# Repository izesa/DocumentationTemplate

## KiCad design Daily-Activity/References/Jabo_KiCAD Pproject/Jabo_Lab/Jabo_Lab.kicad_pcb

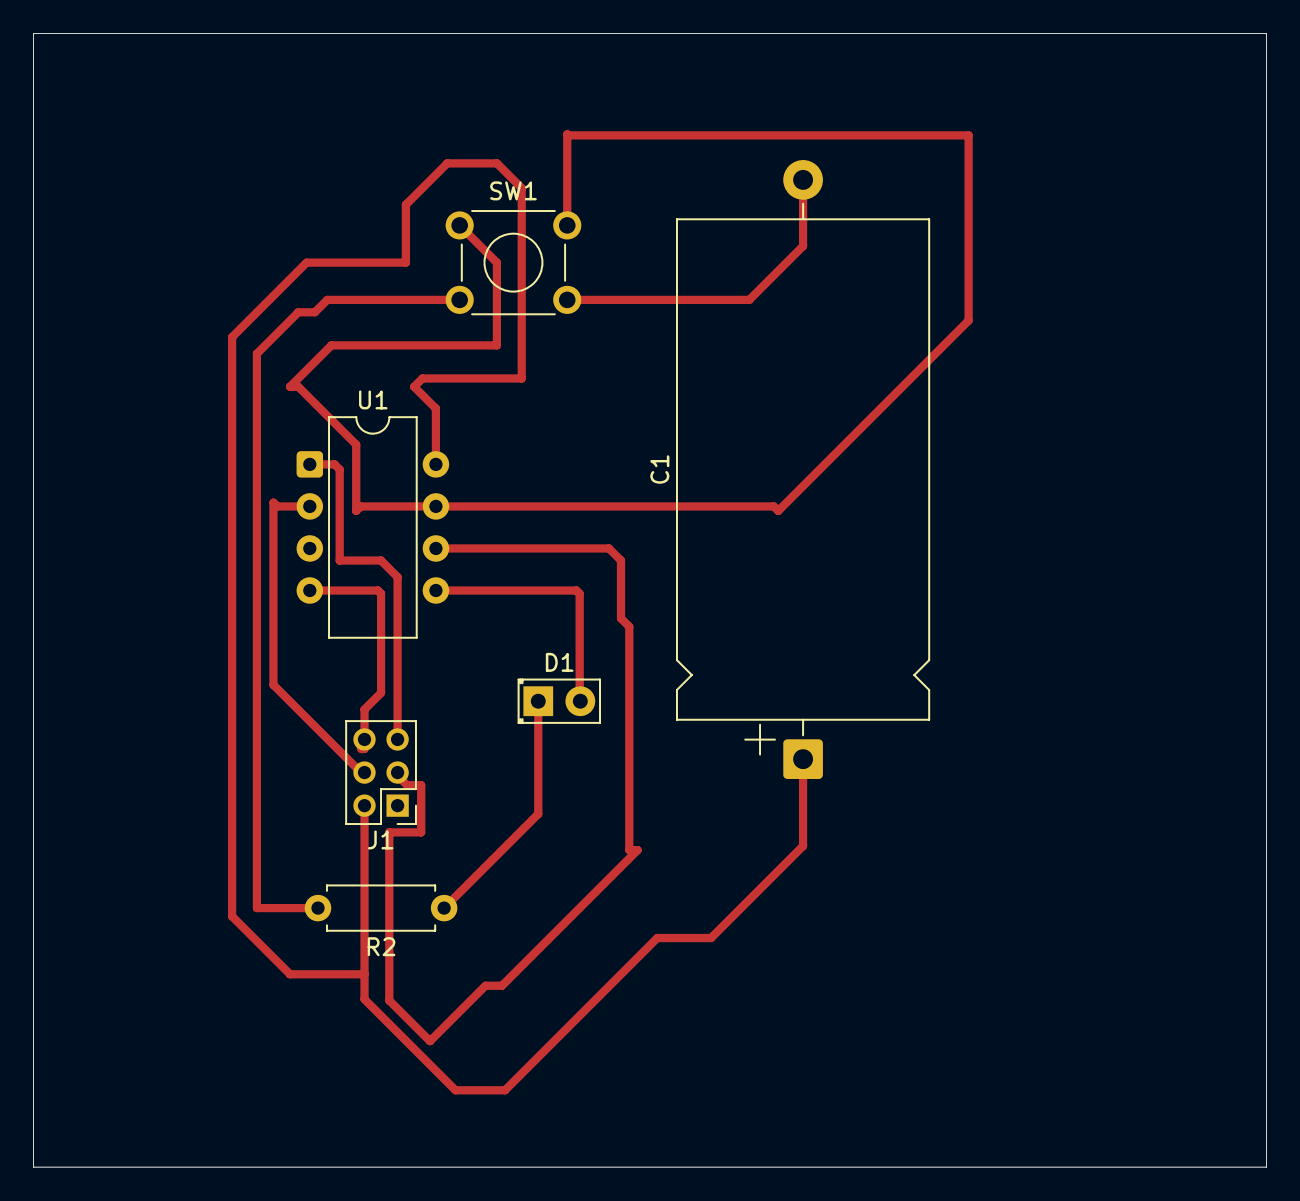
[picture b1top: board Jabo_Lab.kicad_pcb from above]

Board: 2 copper layers, 74.5 x 68.5 mm, 6 parts (0 on the bottom side), 9 nets.

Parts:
C1: 0.1 µF; CP_Axial_L30.0mm_D15.0mm_P35.00mm_Horizontal
D1: LED; LED_D2.0mm_W4.8mm_H2.5mm_FlatTop
J1: AVR-ISP-6; PinHeader_2x03_P2.00mm_Vertical
R2: 220Ohm; R_Axial_DIN0207_L6.3mm_D2.5mm_P7.62mm_Horizontal
SW1: SW_Push; SW_TH_Tactile_Omron_B3F-102x
U1: ATtiny45-20P; CERDIP-8_W7.62mm_SideBrazed

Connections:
5V: C1.1, J1.2 (VCC), U1.8 (VCC)
GND: C1.2, J1.6 (GND), R2.2, SW1.2, U1.4 (GND)
unnamed: D1.2 (A), U1.5 (AREF/PB0)
unnamed: D1.1 (K), R2.1
unnamed: J1.0 (MISO), U1.3 (XTAL2/PB4)
unnamed: J1.4 (MOSI), U1.2 (XTAL1/PB3)
unnamed: J1.3 (SCK), U1.6 (PB1)
unnamed: J1.5 (~RST), U1.1 (~RESET/PB5)
unnamed: SW1.1, U1.7 (PB2)

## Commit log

2026-01-27 the image of IZESA_Jabo in the docs folder will be used at the home page.
2026-01-27 modified: docs/index.md
2026-01-27 renamed: docs/IZESA_Jabo.JPG -> docs/images/IZESA_Jabo.JPG
2026-01-27 modified: docs/index.md
2026-01-27 modified: docs/index.md modified: mkdocs.yml
2026-01-27 modified: docs/Daily-Activity/day_1.md
2026-01-27 new file: docs/Daily-Activity/FreeCad.jpg modified: docs/Daily-Activity/day_2.md
2026-01-27 modified: docs/Daily-Activity/day_2.md renamed: docs/Daily-Activity/FreeCad.jpg -> m docs/files/FreeCad.jpg
2026-01-27 modified: docs/Daily-Activity/day_2.md renamed: docs/files/FreeCad.jpg -> docs/images/FreeCad.jpg
2026-01-27 modified: docs/Daily-Activity/day_2.md renamed: docs/images/FreeCad.jpg -> docs/images/FreeCAD_1.jpg
2026-01-27 new file: Daily-Activity/images/FreeCAD_2.jpg modified: docs/Daily-Activity/day_2.md
2026-01-27 renamed: Daily-Activity/images/FreeCAD_2.jpg -> docs/Daily-Activity/images/FreeCAD_2.jpg
2026-01-27 modified: docs/Daily-Activity/day_2.md
2026-01-27 modified: docs/Daily-Activity/day_2.md new file: docs/Daily-Activity/images/Day_2.jpg
2026-01-27 modified: docs/Daily-Activity/day_1.md
2026-01-27 modified: docs/index.md
2026-01-27 modified: docs/Daily-Activity/day_4.md
2026-01-29 modified: docs/Daily-Activity/day_5.md
2026-01-30 modified: mkdocs.yml
2026-01-30 modified: docs/Daily-Activity/index.md
2026-01-30 modified: docs/Daily-Activity/day_3.md new file: docs/Daily-Activity/images/KiCAD_Project.png
2026-01-30 modified: docs/Daily-Activity/day_3.md new file: docs/Daily-Activity/images/KiCAD_Project02.png
2026-01-30 modified: docs/Daily-Activity/day_3.md
2026-01-30 new file: docs/Daily-Activity/References/Jabo_KiCAD Pproject/Jabo_Lab/124444/Jabo_Lab-Edge_Cuts.gbr new file: docs/Daily-Activity/References/Jabo_KiCAD Pproject/Jabo_Lab/124444/Jabo_Lab-F_Cu.gbr new 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
2026-01-30 new file: docs/Daily-Activity/References/Jabo_KiCAD Pproject/Jabo_Lab/index.md
2026-01-30 modified: docs/Daily-Activity/References/Jabo_KiCAD Pproject/Jabo_Lab/index.md modified: mkdocs.yml
2026-01-30 deleted: docs/Daily-Activity/References/Jabo_KiCAD Pproject/Jabo_Lab/index.md modified: mkdocs.yml
2026-01-30 deleted: docs/Daily-Activity/day_6.md deleted: docs/Daily-Activity/day_7.md deleted: docs/Daily-Activity/day_8.md deleted: docs/Daily-Activity/day_9.md
2026-02-03 Deployed 4bfbb07 with MkDocs version: 1.6.1
2026-02-03 Deployed b55c1e8 with MkDocs version: 1.6.1
2026-02-03 Deployed aca9aef with MkDocs version: 1.6.1
2026-02-03 adding steps
2026-02-03 Adding indexpag
2026-02-03 Add GitHub Actions workflow for GitHub Pages deployment
    This workflow automates the deployment of static content to GitHub Pages upon pushes to the main branch or manually via the Actions tab.
2026-02-03 Add GitHub Actions workflow for Jekyll deployment
    This workflow builds and deploys a Jekyll site to GitHub Pages, with steps for checking out the code, setting up pages, building the site, and deploying it.
2026-02-03 Add GitHub Actions workflow for Jekyll deployment
2026-02-03 Deployed d6eca8a with MkDocs version: 1.6.1
2026-02-03 Fixing Daily-Activity folder
2026-02-03 Deployed 9a2fe1f with MkDocs version: 1.6.1
2026-02-03 Deployed df8d79b with MkDocs version: 1.6.1
2026-02-03 renamed: docs/images/Day_2_Act.png -> docs/Daily-Activity/images/Day_2_Act.png
2026-02-03 Deployed e428c82 with MkDocs version: 1.6.1
2026-02-03 Deployed 5bf799a with MkDocs version: 1.6.1
2026-02-03 Deployed 412315a with MkDocs version: 1.6.1
2026-02-03 new file: docs/Daily-Activity/images/Day_3_Act.jpg new file: docs/Daily-Activity/images/Day_4_Act.png modified: docs/Daily-Activity/index.md
2026-02-03 Deployed ce41a37 with MkDocs version: 1.6.1
2026-02-03 Deployed 92f6264 with MkDocs version: 1.6.1
2026-02-03 new file: docs/Daily-Activity/images/Day_5_Act.png modified: docs/Daily-Activity/index.md
2026-02-03 Deployed 59f108f with MkDocs version: 1.6.1
